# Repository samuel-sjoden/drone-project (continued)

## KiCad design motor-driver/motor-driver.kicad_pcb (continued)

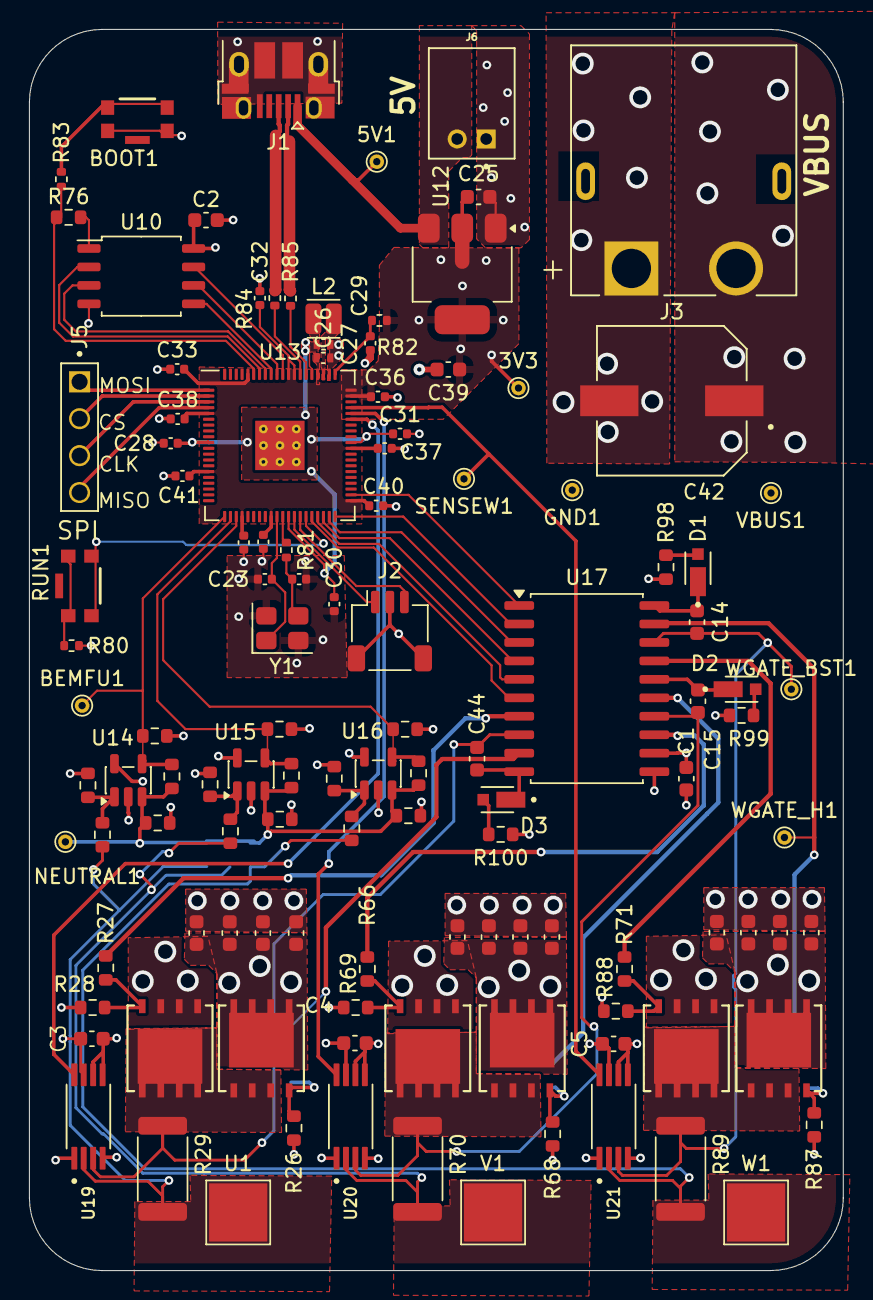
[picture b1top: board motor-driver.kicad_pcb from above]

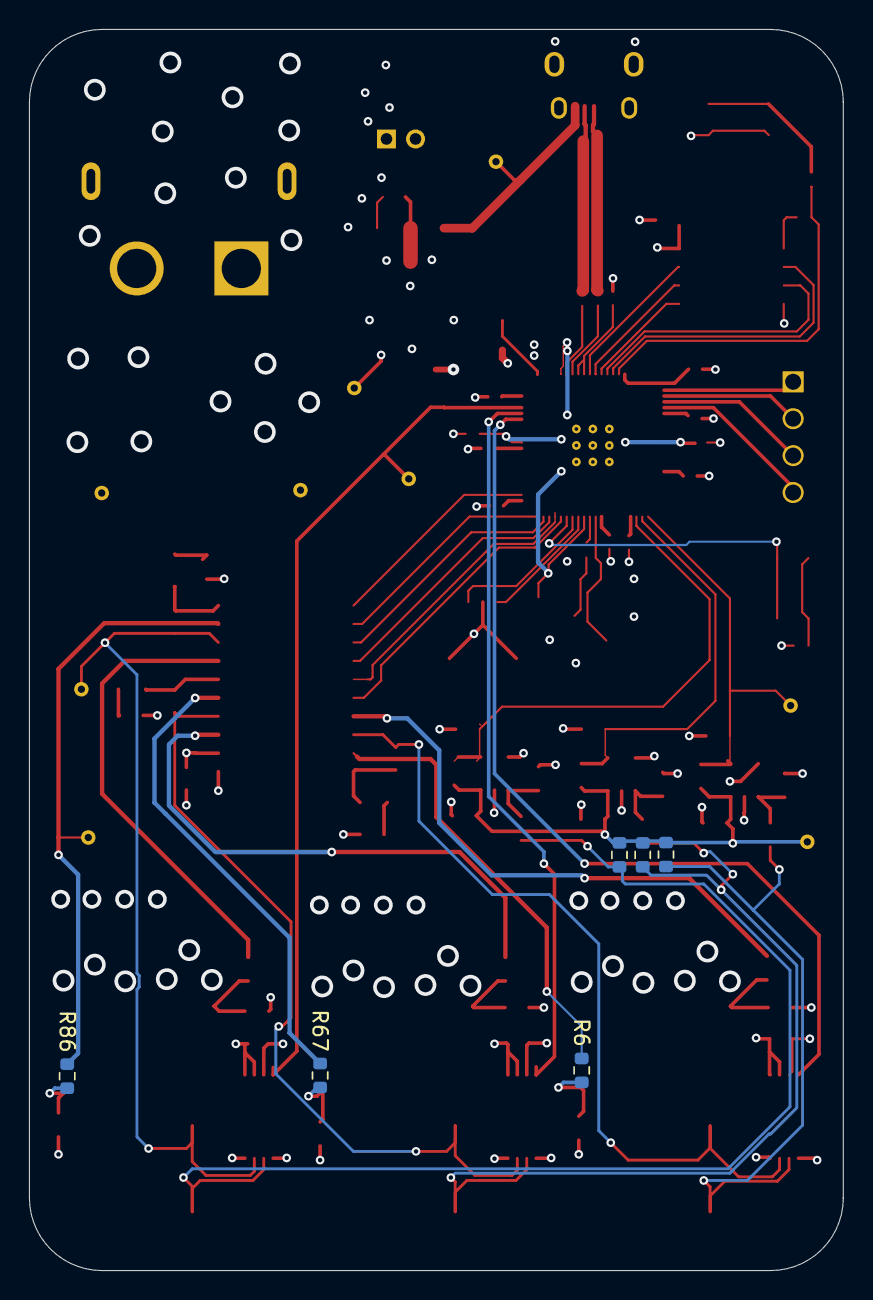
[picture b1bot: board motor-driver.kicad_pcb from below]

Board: 4 copper layers, 56.0 x 85.4 mm, 123 parts (6 on the bottom side), 70 nets.

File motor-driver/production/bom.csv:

Designator,Footprint,Quantity,Value,LCSC Part #
"BOOT1, RUN1",SW_Push_1P1T_NO_Vertical_Wuerth_434133025816,2,434133025816,
C1,0603,1,1uF,
"C14, C15, C3, C4, C44, C5",0603,6,0.1uF,
"C2, C28, C31, C32, C33, C34, C35, C36, C37, C38, C40, C41",0402,12,100n,
"C23, C24",0402,2,15p,
"C25, C39",0603,2,10u,
"C26, C27, C29, C30",0402,4,4.7u,
C42,CAPAE1030X1225N,1,330uF,
"C43, C53, C54, C55, C56, C57, C58, C59, C60, C61, C62, C8",0603,12,GRM188R6YA106MA73D,
"D1, D2, D3",DIO_MSS1P6-M3_89A,3,MSS1P6-M3_89A,
J1,USB_Micro-B_Amphenol_10103594-0001LF_Horizontal,1,10103594-0001LF,
J2,JST_SH_SM03B-SRSS-TB_1x03-1MP_P1.00mm_Horizontal,1,SM03B-SRSS-TB,
J3,AMASS_XT60PW-F,1,XT60PW-F,
J4,JST_B2B-PH-SM4-TB,1,B2B-PH-SM4-TB,
J5,JST_S4B-XH-A,1,S4B-XH-A,
L2,L_Cenker_CKCS201610,1,AOTA-B201610S3R3-101-T,
"MOSFET1, MOSFET10, MOSFET2, MOSFET7, MOSFET8, MOSFET9",DFN5X6_8L_EP1_P_AOS,6,AON6512,
"R100, R98, R99",0603,3,50,
"R26, R28, R30, R31, R32, R34, R35, R36, R55, R57, R68, R69, R87, R88, R90, R91, R92, R94, R95, R96, R97",0603,21,10k,
"R27, R6, R66, R67, R71, R86",0603,6,22,
"R29, R70, R89",2512,3,5m,
"R33, R56, R93",0603,3,1M,
R76,0402,1,0,
"R80, R81, R83",0402,3,1k,
R82,0402,1,33,
"R84, R85",0402,2,27,
U10,SOIC-8_5.23x5.23mm_P1.27mm,1,W25Q128JVS,
U12,SOT-223-3_TabPin2,1,NCP1117ST33T3G,
U13,RP2350-QFN-80-1EP_10x10_P0.4mm_EP3.4x3.4mm_ThermalVias,1,RP2350B,
"U14, U15, U16",SOT-23-5,3,LM397,
U17,SOIC-20W_7.5x12.8mm_P1.27mm,1,FAN7388,
"U19, U20, U21",SOP65P640X120-8N,3,INA240A1PWR,
Y1,Crystal_SMD_3225-4Pin_3.2x2.5mm,1,ABM8-272-T3,

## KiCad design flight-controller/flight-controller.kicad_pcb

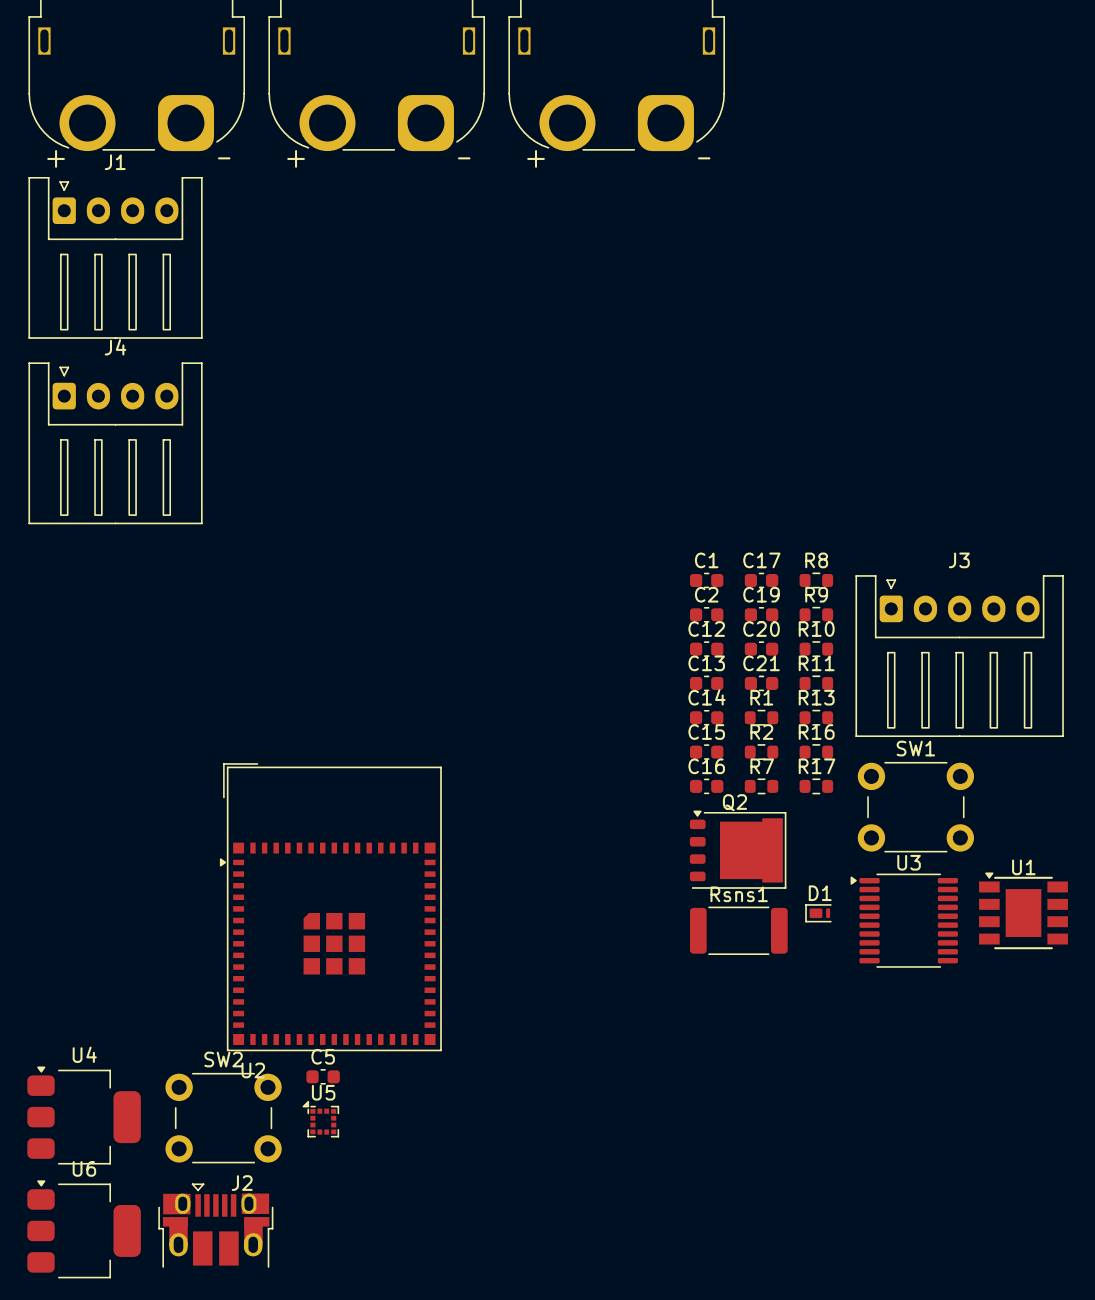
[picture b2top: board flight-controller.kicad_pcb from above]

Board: 2 copper layers, 40 parts (0 on the bottom side), 35 nets, no tracks yet.

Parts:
C1, C12, C16, C17, C19, C20, C21: 1u; C_0603_1608Metric
C2, C5: 10u; C_0603_1608Metric
C13, C14, C15: 0.1u; C_0603_1608Metric
D1: PTVS18VZ1USK; Nexperia_DSN1608-2_1.6x0.8mm
J1: MD1_SPI; JST_XH_S4B-XH-A_1x04_P2.50mm_Horizontal
J2: USB_B_Micro; USB_Micro-B_Amphenol_10103594-0001LF_Horizontal
J3: Lipo JST; JST_XH_S5B-XH-A_1x05_P2.50mm_Horizontal
J4: MD2_SPI; JST_XH_S4B-XH-A_1x04_P2.50mm_Horizontal
J8: XT60PW-F; AMASS_XT60PW-F_1x02_P7.20mm_Horizontal
J9: MD1_15V; AMASS_XT60PW-F_1x02_P7.20mm_Horizontal
J10: MD2_15V; AMASS_XT60PW-F_1x02_P7.20mm_Horizontal
Q2: NMOS; PQFN-8-EP_6x5mm_P1.27mm_Generic
R1, R2, R9, R10, R11, R13, R16: 100; R_0603_1608Metric
R7: 1M; R_0603_1608Metric
R8, R17: 10k; R_0603_1608Metric
Rsns1: 5m; R_2512_6332Metric
SW1: SW_Push; SW_PUSH_6mm
SW2: RESET; SW_PUSH_6mm
U1: AP64500SP-13; Diodes_SO-8EP
U2: ESP32-S3-MINI-1; ESP32-S2-MINI-1
U3: BQ76920PW; TSSOP-20_4.4x6.5mm_P0.65mm
U4: NCP1117ST33T3G; SOT-223-3_TabPin2
U5: LIS2MDL; LGA-12_2x2mm_P0.5mm
U6: NCP1117-1.8_SOT223; SOT-223-3_TabPin2

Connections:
3V3: C5.1, U2.3 (3V3), U4.2 (VO)
5V: J2.1 (VBUS), U4.3 (VI), U6.3 (VI)
+1V8: U5.9 (Vdd), U5.10 (Vdd_IO), U6.2 (VO)
/BMS/15V: C12.1, D1.1 (K), J8.1, J9.1, J10.1, R1.1, U1.2 (VIN), U1.3 (EN), U3.9 (REGSRC)
/BMS/INT_BMS: U2.10 (IO6), U3.20 (ALERT)
/BMS/PWR_BTN: R8.1, R17.1, U2.5 (IO1), U3.6 (TS1)
/Flight_Controller/CS_MD1: J1.3, U2.31 (IO35)
/Flight_Controller/CS_MD2: J4.3, U2.32 (IO36)
/Flight_Controller/MISO: J1.1, J4.1, U2.17 (IO13)
/Flight_Controller/MOSI: J1.4, J4.4, U2.15 (IO11)
/Flight_Controller/SCL: U2.12 (IO8), U3.5 (SCL)
/Flight_Controller/SCLK: J1.2, J4.2, U2.16 (IO12)
/Flight_Controller/SDA: U2.13 (IO9), U3.4 (SDA)
GND: C1.2, C2.2, C12.2, C14.1, C15.2, C16.2, C17.1, J8.2 (N), R8.2, R11.1, Rsns1.1, U3.3 (VSS)
GND1: C5.2, D1.2 (A), J2.5 (GND), J2.SH (Shield), J9.2 (N), J10.2 (N), Q2.1 (D), SW2.1, U1.7 (GND), U2.1 (GND), U2.2 (GND), U2.42 (GND), U2.43 (GND), U2.46 (GND), U2.47 (GND), U2.48 (GND), U2.49 (GND), U2.50 (GND), U2.51 (GND), U2.52 (GND), U2.53 (GND), U2.54 (GND), U2.55 (GND), U2.56 (GND), U2.57 (GND), U2.58 (GND), U2.59 (GND), U2.60 (GND), U2.61 (GND), U2.62 (GND), U2.63 (GND), U2.64 (GND), U2.65 (GND), U4.1 (GND), U5.6 (GND), U5.8 (GND), U6.1 (GND)
unnamed: J2.3 (D+), U2.24 (USB_D+)
unnamed: J2.2 (D-), U2.23 (USB_D-)
unnamed: J3.1, R9.1
unnamed: J3.2, R10.1
unnamed: J3.3, R13.1
unnamed: J3.4, R2.1
unnamed: J3.5, R16.1
unnamed: Q2.2 (G), R7.1, U3.1 (DSG)
unnamed: Q2.3 (S), R7.2, Rsns1.2
unnamed: R17.2, SW1.1
unnamed: SW2.2, U2.45 (EN)
unnamed: C2.1, R1.2, U3.10 (BAT)
unnamed: C1.1, U3.7 (CAP1)
unnamed: C13.1, C14.2, U3.19 (SRN)
unnamed: C13.2, C15.1, R11.2, U3.18 (SRP)
unnamed: C17.2, R9.2, U3.17 (VC0)
unnamed: C16.1, C19.2, R10.2, SW1.2, U3.16 (VC1)
unnamed: C19.1, C20.2, R13.2, U3.15 (VC2)
unnamed: C20.1, C21.2, R2.2, U3.13 (VC4), U3.14 (VC3)
unnamed: C21.1, R16.2, U3.12 (VC5)

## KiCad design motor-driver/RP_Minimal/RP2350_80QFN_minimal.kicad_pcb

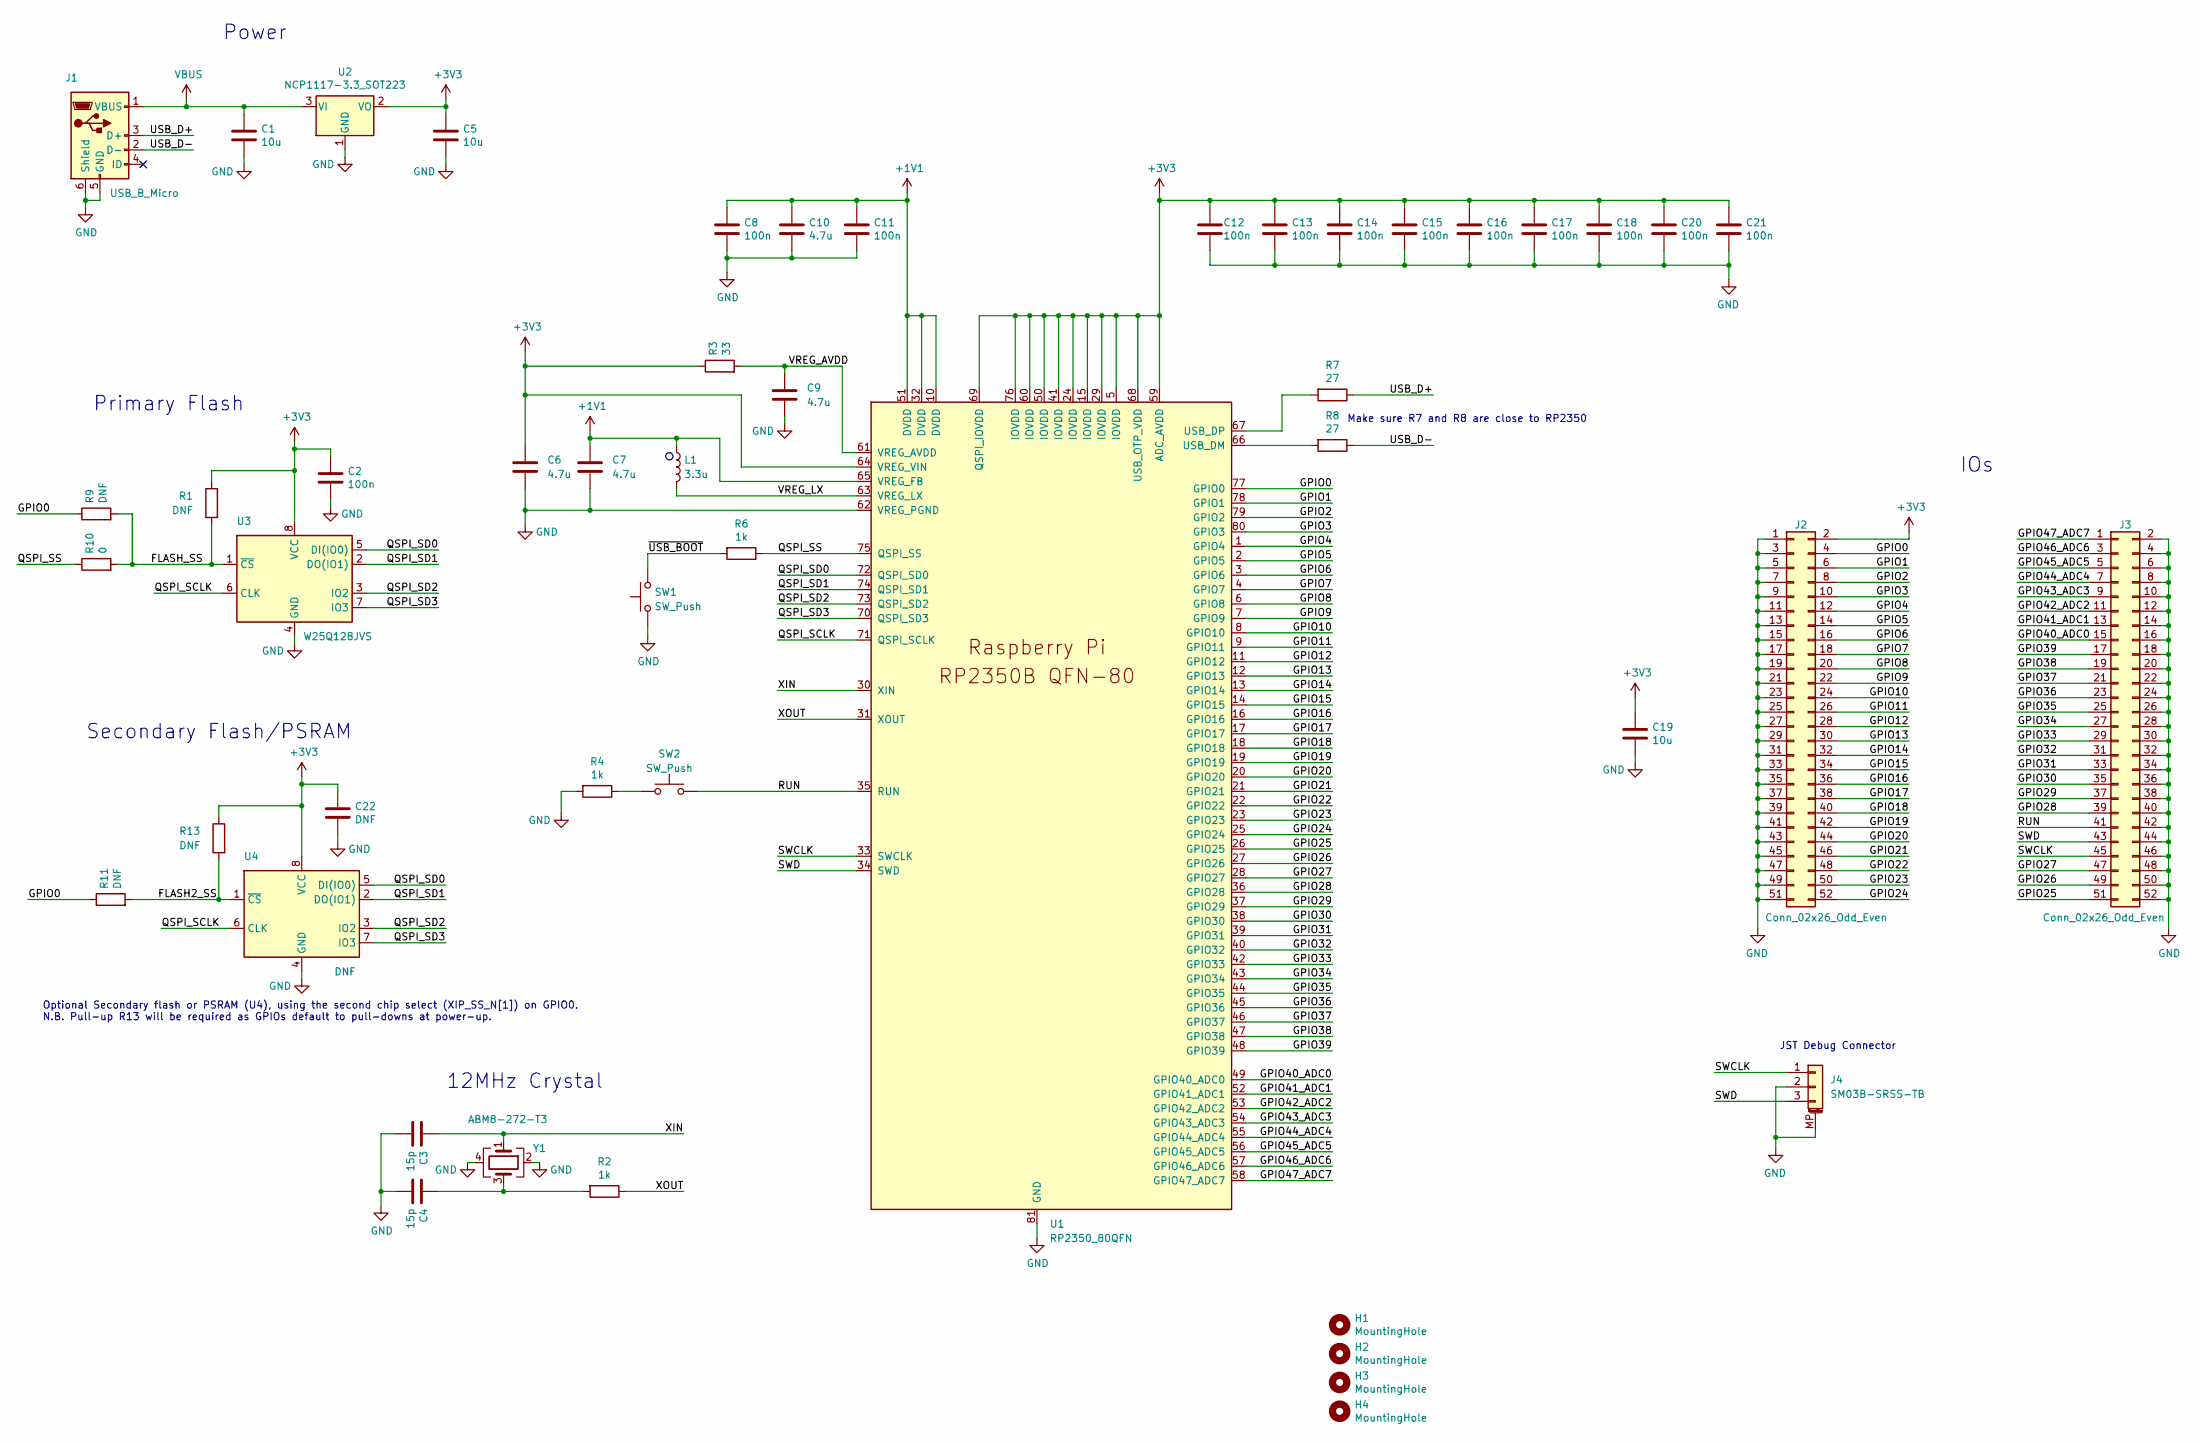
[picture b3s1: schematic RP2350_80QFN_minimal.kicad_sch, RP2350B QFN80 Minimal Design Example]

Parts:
C1, C5, C19: 10u; C_0805_2012Metric
C2, C8, C11, C12, C13, C14, C15, C16, C17, C18, C20, C21: 100n; C_0402_1005Metric
C3, C4: 15p; C_0402_1005Metric
C6, C7: 4.7u; C_0402_1005Metric_small_pads
C9, C10: 4.7u; C_0402_1005Metric
C22: DNF; C_0402_1005Metric
H1, H2, H3, H4: MountingHole; MountingHole_2.7mm_M2.5
J1: USB_B_Micro; USB_Micro-B_Amphenol_10103594-0001LF_Horizontal
J2, J3: Conn_02x26_Odd_Even; PinHeader_2x26_P2.54mm_Vertical
J4: SM03B-SRSS-TB; JST_SH_SM03B-SRSS-TB_1x03-1MP_P1.00mm_Horizontal
L1: 3.3u; L_pol_2016
R1, R9, R11, R13: DNF; R_0402_1005Metric
R2, R4, R6: 1k; R_0402_1005Metric
R3: 33; R_0402_1005Metric
R7, R8: 27; R_0402_1005Metric
R10: 0; R_0402_1005Metric
SW1, SW2: SW_Push; SW_Push_1P1T_NO_Vertical_Wuerth_434133025816
U1: RP2350_80QFN; RP2350-QFN-80-1EP_10x10_P0.4mm_EP3.4x3.4mm_ThermalVias
U2: NCP1117-3.3_SOT223; SOT-223-3_TabPin2
U3: W25Q128JVS; SOIC-8_5.23x5.23mm_P1.27mm
U4: DNF; SOIC-8_5.23x5.23mm_P1.27mm
Y1: ABM8-272-T3; Crystal_SMD_3225-4Pin_3.2x2.5mm

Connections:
+1V1: C7.1, C8.1, C10.1, C11.1, L1.1, U1.10 (DVDD), U1.32 (DVDD), U1.51 (DVDD), U1.65 (VREG_FB)
+3V3: C2.1, C5.1, C6.1, C12.1, C13.1, C14.1, C15.1, C16.1, C17.1, C18.1, C19.1, C20.1, C21.1, C22.1, J2.2, R1.1, R3.1, R13.1, U1.5 (IOVDD), U1.15 (IOVDD), U1.24 (IOVDD), U1.29 (IOVDD), U1.41 (IOVDD), U1.50 (IOVDD), U1.59 (ADC_AVDD), U1.60 (IOVDD), U1.64 (VREG_VIN), U1.68 (USB_OTP_VDD), U1.69 (QSPI_IOVDD), U1.76 (IOVDD), U2.2 (VO), U3.8 (VCC), U4.8 (VCC)
/FLASH2_SS: R11.2, R13.2, U4.1 (~CS)
/FLASH_SS: R1.2, R9.2, R10.2, U3.1 (~CS)
/GPIO0: J2.4, R9.1, R11.1, U1.77 (GPIO0)
/GPIO1: J2.6, U1.78 (GPIO1)
/GPIO2: J2.8, U1.79 (GPIO2)
/GPIO3: J2.10, U1.80 (GPIO3)
/GPIO4: J2.12, U1.1 (GPIO4)
/GPIO5: J2.14, U1.2 (GPIO5)
/GPIO6: J2.16, U1.3 (GPIO6)
/GPIO7: J2.18, U1.4 (GPIO7)
/GPIO8: J2.20, U1.6 (GPIO8)
/GPIO9: J2.22, U1.7 (GPIO9)
/GPIO10: J2.24, U1.8 (GPIO10)
/GPIO11: J2.26, U1.9 (GPIO11)
/GPIO12: J2.28, U1.11 (GPIO12)
/GPIO13: J2.30, U1.12 (GPIO13)
/GPIO14: J2.32, U1.13 (GPIO14)
/GPIO15: J2.34, U1.14 (GPIO15)
/GPIO16: J2.36, U1.16 (GPIO16)
/GPIO17: J2.38, U1.17 (GPIO17)
/GPIO18: J2.40, U1.18 (GPIO18)
/GPIO19: J2.42, U1.19 (GPIO19)
/GPIO20: J2.44, U1.20 (GPIO20)
/GPIO21: J2.46, U1.21 (GPIO21)
/GPIO22: J2.48, U1.22 (GPIO22)
/GPIO23: J2.50, U1.23 (GPIO23)
/GPIO24: J2.52, U1.25 (GPIO24)
/GPIO25: J3.51, U1.26 (GPIO25)
/GPIO26: J3.49, U1.27 (GPIO26)
/GPIO27: J3.47, U1.28 (GPIO27)
/GPIO28: J3.39, U1.36 (GPIO28)
/GPIO29: J3.37, U1.37 (GPIO29)
/GPIO30: J3.35, U1.38 (GPIO30)
/GPIO31: J3.33, U1.39 (GPIO31)
/GPIO32: J3.31, U1.40 (GPIO32)
/GPIO33: J3.29, U1.42 (GPIO33)
/GPIO34: J3.27, U1.43 (GPIO34)
/GPIO35: J3.25, U1.44 (GPIO35)
/GPIO36: J3.23, U1.45 (GPIO36)
/GPIO37: J3.21, U1.46 (GPIO37)
/GPIO38: J3.19, U1.47 (GPIO38)
/GPIO39: J3.17, U1.48 (GPIO39)
/GPIO40_ADC0: J3.15, U1.49 (GPIO40_ADC0)
/GPIO41_ADC1: J3.13, U1.52 (GPIO41_ADC1)
/GPIO42_ADC2: J3.11, U1.53 (GPIO42_ADC2)
/GPIO43_ADC3: J3.9, U1.54 (GPIO43_ADC3)
/GPIO44_ADC4: J3.7, U1.55 (GPIO44_ADC4)
/GPIO45_ADC5: J3.5, U1.56 (GPIO45_ADC5)
/GPIO46_ADC6: J3.3, U1.57 (GPIO46_ADC6)
/GPIO47_ADC7: J3.1, U1.58 (GPIO47_ADC7)
/QSPI_SCLK: U1.71 (QSPI_SCLK), U3.6 (CLK), U4.6 (CLK)
/QSPI_SD0: U1.72 (QSPI_SD0), U3.5 (DI(IO0)), U4.5 (DI(IO0))
/QSPI_SD1: U1.74 (QSPI_SD1), U3.2 (DO(IO1)), U4.2 (DO(IO1))
/QSPI_SD2: U1.73 (QSPI_SD2), U3.3 (IO2), U4.3 (IO2)
/QSPI_SD3: U1.70 (QSPI_SD3), U3.7 (IO3), U4.7 (IO3)
/QSPI_SS: R6.1, R10.1, U1.75 (QSPI_SS)
/RUN: J3.41, SW2.2, U1.35 (RUN)
/SWCLK: J3.45, J4.1, U1.33 (SWCLK)
/SWD: J3.43, J4.3, U1.34 (SWD)
/USB_D+: J1.3 (D+), R7.1
/USB_D-: J1.2 (D-), R8.1
/VREG_AVDD: C9.1, R3.2, U1.61 (VREG_AVDD)
/VREG_LX: L1.2, U1.63 (VREG_LX)
/XIN: C3.1, U1.30 (XIN), Y1.1
/XOUT: R2.1, U1.31 (XOUT)
/~USB_BOOT: R6.2, SW1.2
GND: C1.2, C2.2, C3.2, C4.2, C5.2, C6.2, C7.2, C8.2, C9.2, C10.2, C11.2, C12.2, C13.2, C14.2, C15.2, C16.2, C17.2, C18.2, C19.2, C20.2, C21.2, C22.2, J1.5 (GND), J1.6 (Shield), J2.1, J2.3, J2.5, J2.7, J2.9, J2.11, J2.13, J2.15, J2.17, J2.19, J2.21, J2.23, J2.25, J2.27, J2.29, J2.31, J2.33, J2.35, J2.37, J2.39, J2.41, J2.43, J2.45, J2.47, J2.49, J2.51, J3.2, J3.4, J3.6, J3.8, J3.10, J3.12, J3.14, J3.16, J3.18, J3.20, J3.22, J3.24, J3.26, J3.28, J3.30, J3.32, J3.34, J3.36, J3.38, J3.40, J3.42, J3.44, J3.46, J3.48, J3.50, J3.52, J4.2, J4.MP (MountPin), R4.2, SW1.1, U1.62 (VREG_PGND), U1.81 (GND), U2.1 (GND), U3.4 (GND), U4.4 (GND), Y1.2, Y1.4
unnamed: C4.1, R2.2, Y1.3
unnamed: R4.1, SW2.1
unnamed: R8.2, U1.66 (USB_DM)
unnamed: R7.2, U1.67 (USB_DP)
VBUS: C1.1, J1.1 (VBUS), U2.3 (VI)

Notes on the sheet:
Optional Secondary flash or PSRAM (U4), using the second chip select (XIP_SS_N[1]) on GPIO0. N.B. Pull-up R13 will be required as GPIOs default to pull-downs at power-up.
IOs
12MHz Crystal
Primary Flash
JST Debug Connector
Make sure R7 and R8 are close to RP2350
Secondary Flash/PSRAM
Power

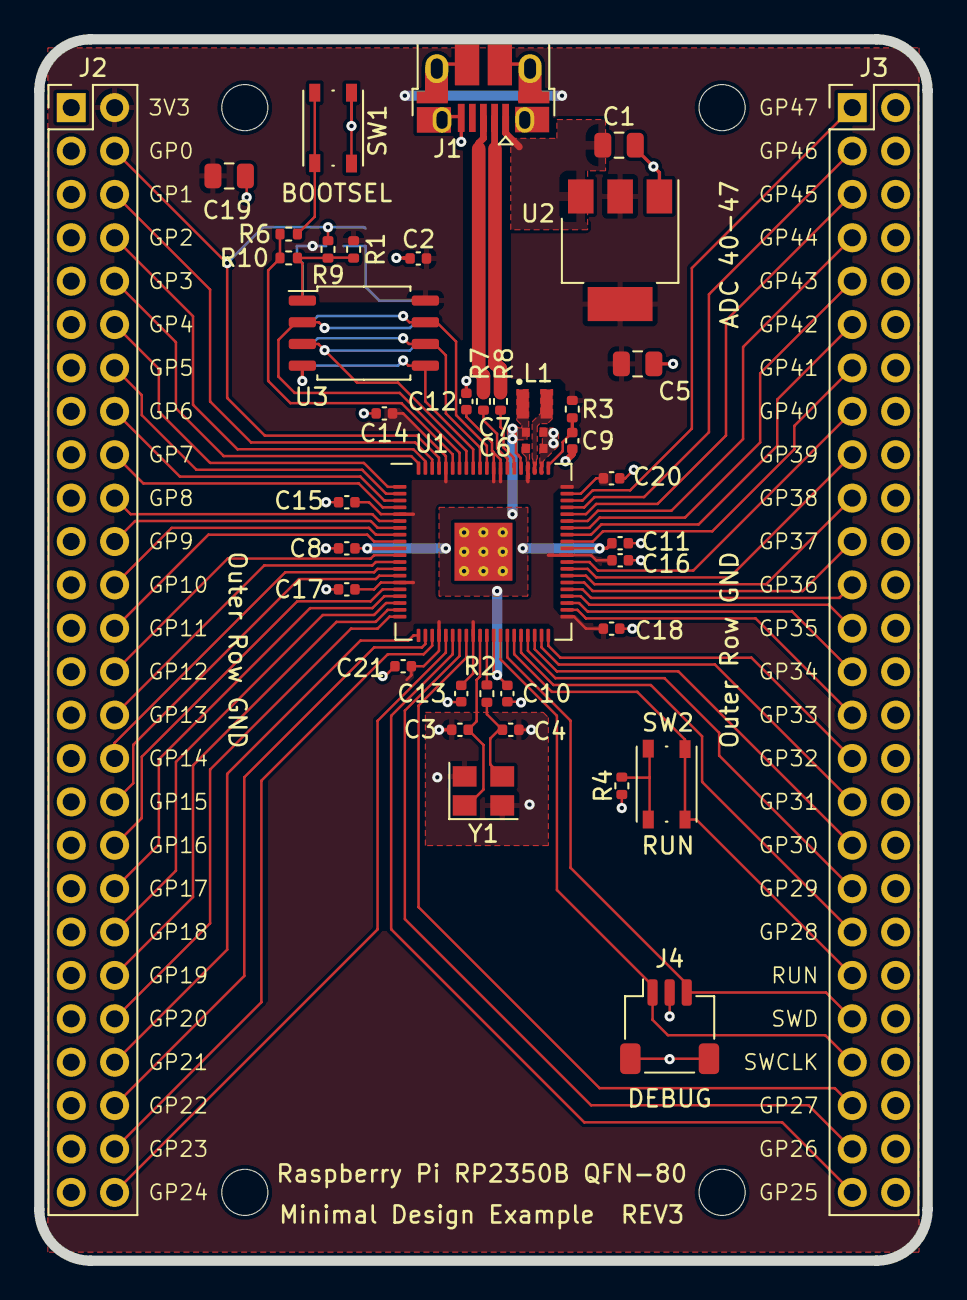
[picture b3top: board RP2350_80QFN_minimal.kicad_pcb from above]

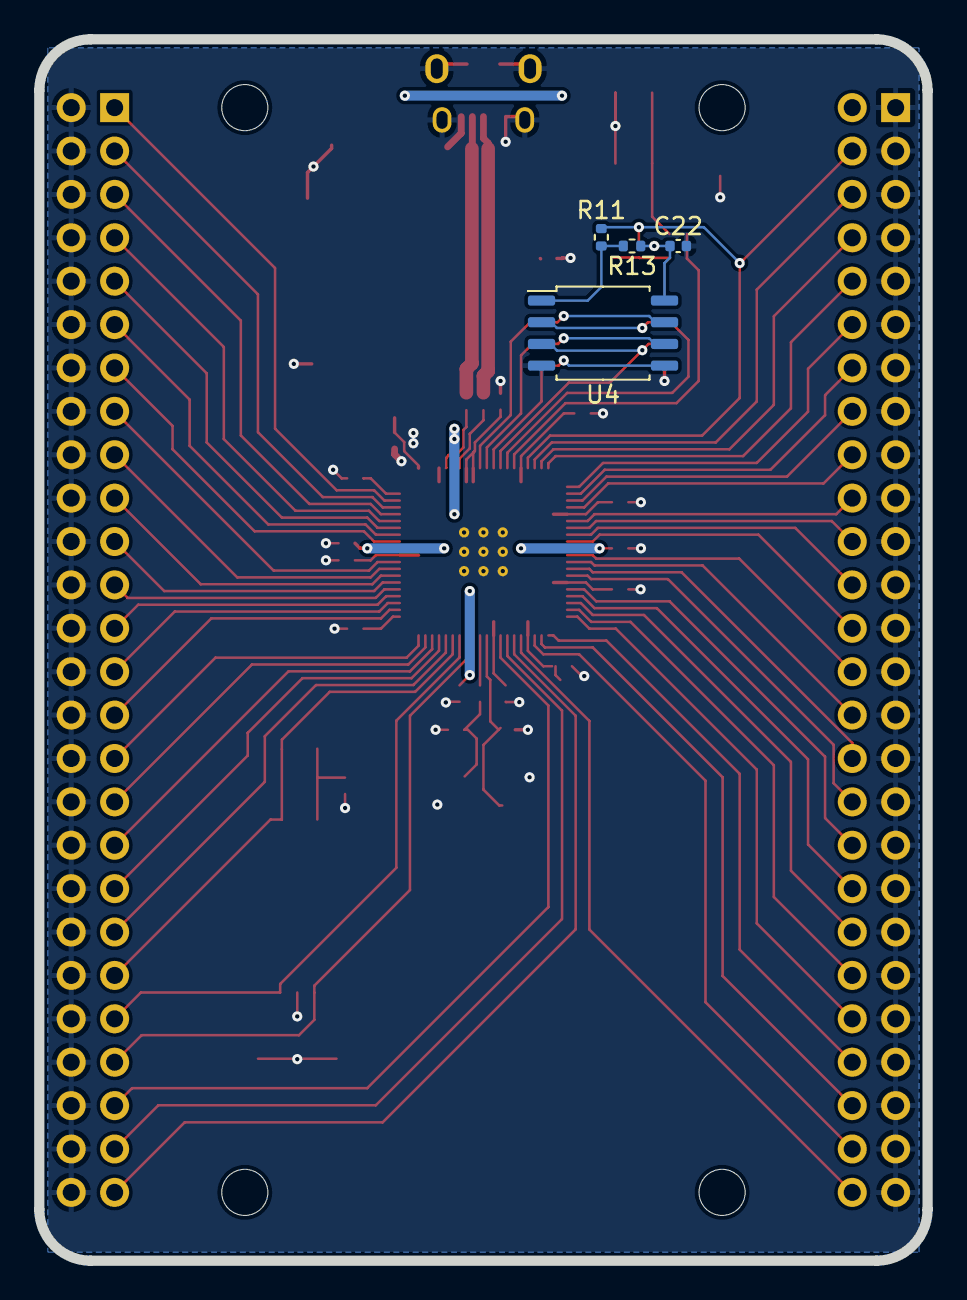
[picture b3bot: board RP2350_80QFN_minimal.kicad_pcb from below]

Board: 2 copper layers, 52.0 x 71.5 mm, 49 parts (4 on the bottom side), 74 nets.

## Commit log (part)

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2026-01-15 added gitignore
2026-01-15 Initial plan
2026-01-15 Add Python drone simulation project with tests
2026-01-15 Address code review feedback: remove unused import, add timestamps to logs
2026-01-16 started open loop code
2026-01-16 fixed gitignore
2026-01-17 finished open loop logic
2026-01-17 fix to espressif api call
2026-01-17 moved open loop code into esp project
2026-01-18 added compile commands in cmake and packed states into 32 bit integer
2026-01-18 fixed implicit cast to uint32_t
2026-01-19 fixed bitmask guy
2026-01-19 added flake for open-loop
2026-01-19 updated gitignore
2026-01-19 goon
2026-01-19 it works!
2026-01-20 made flake system generic
2026-02-19 paritally done svpwm
2026-02-19 software pwm with edge triggered calculations
2026-02-21 added foc file with svpwm logic.
2026-02-21 finished mcpwm svpwm script with sine and cosine LUT
2026-02-22 added inverter setup
2026-02-22 finished svpwm with mcpwm open-loop
2026-02-23 fixed linking and logic bugs with sine look up table
2026-02-23 fixed bugs with testing
2026-02-24 Testing commit
2026-02-27 motor driver schematic updated
2026-02-27 removed zip files from tracking and updated git ignore
2026-02-27 modified bulk capacitor setup
2026-03-09 current sense finshed for motor driver
2026-03-10 completed sheet connections
2026-03-13 added connectors starting pcb layout
2026-03-25 commit before changing custom sullen key sense
2026-03-27 commit before inverter revisions
2026-03-27 post revisions
2026-03-30 routing complete
2026-04-01 added spi connection
2026-04-01 board ready for review
2026-04-01 added test points
2026-04-02 bom finished
2026-04-02 cooking
2026-04-03 flight-controller
2026-04-03 deleted cache
2026-04-03 changed push buttons and zone clearances
2026-04-04 clean hierachy?
2026-04-04 clean hierachy
2026-04-04 fc with esp
2026-04-10 sensors
2026-04-10 reoriented parts
2026-04-12 cleaned up the layout
